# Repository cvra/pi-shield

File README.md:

# CVRA CAN Raspberry Pi Shield

## Features

* Power supply from 12V to 36V to 5V, 3A.
    Powers the Raspberry Pi, and optionally the CAN bus.
* MCP2515 CAN interface (compatible with Linux/SocketCAN) with transceiver and two connectors for daisy chaining.
* Connector for robot's front panel LEDs (dimmable) and pushbuttons.
* Touchscreen connector (I2C for touch, SPI for pixel data)
* DIP switch to discriminate between robots.
* Battery-backed Realtime Clock allows the robot to keep the time even when powered off.
* UART console
* Power control pins, used to cleanly shutdown the Raspberry Pi before shutting power down.
* Socket for a 20 mm DC fan.
* Slot to allow the use of the PiCam camera module.

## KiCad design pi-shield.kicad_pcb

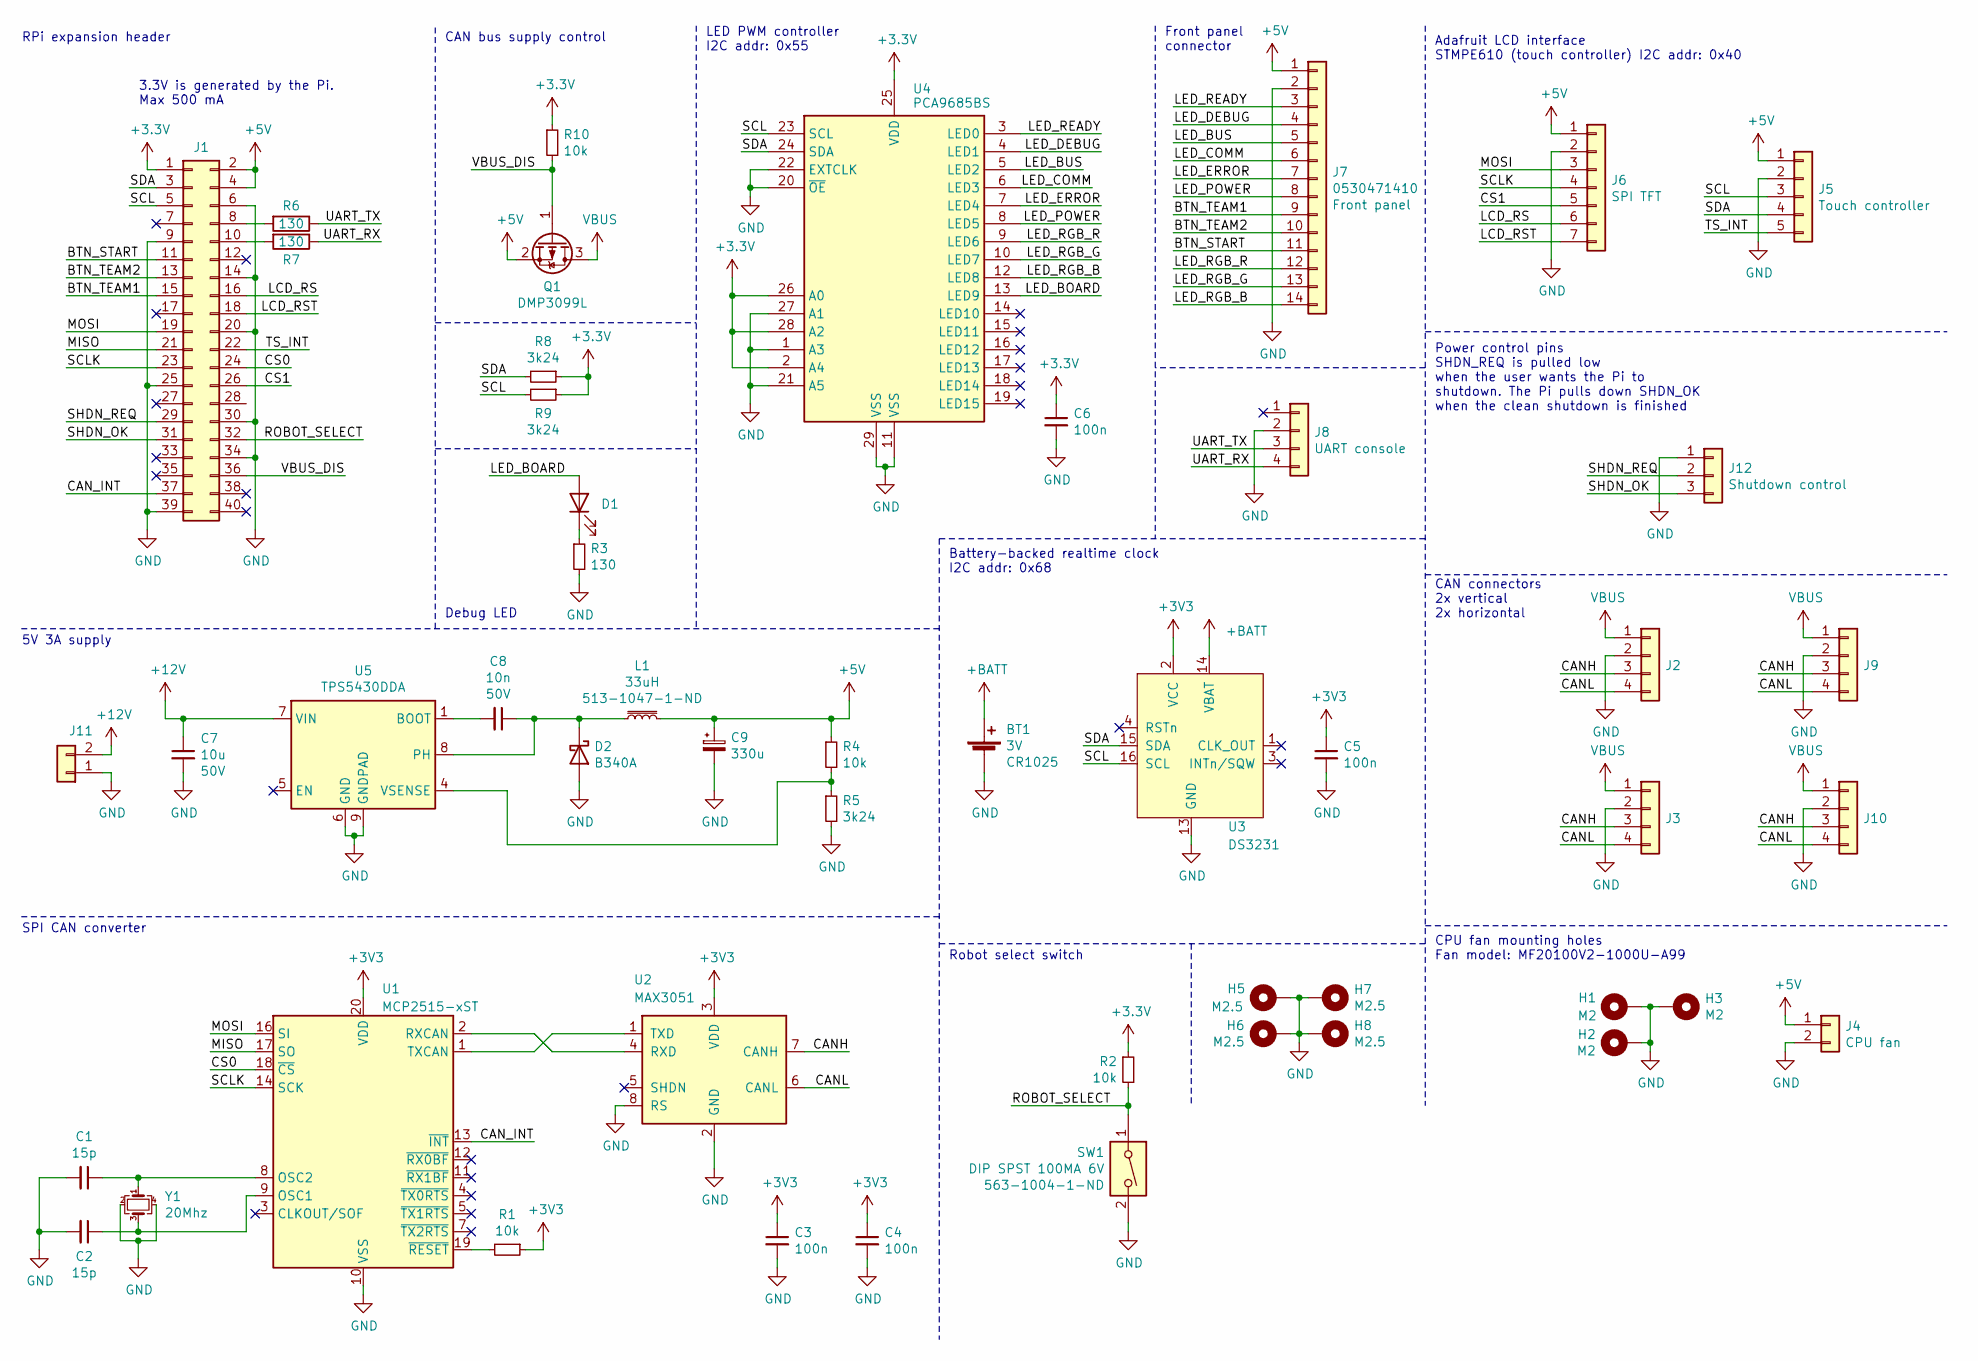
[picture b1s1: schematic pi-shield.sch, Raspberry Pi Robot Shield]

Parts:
BT1: 3V; 3030; digikey# 36-3030-ND
C1: 15p; C_0805_2012Metric_Pad1.15x1.40mm_HandSolder; digikey# 399-17621-1-ND
C2: 15p; C_0805_2012Metric_Pad1.15x1.40mm_HandSolder
C3: 100n; C_0805_2012Metric_Pad1.15x1.40mm_HandSolder; digikey# 399-1169-1-ND
C4, C5, C6: 100n; C_0805_2012Metric_Pad1.15x1.40mm_HandSolder
C7: 10u; C_2220_5650Metric_Pad1.97x5.40mm_HandSolder; voltage 50V; digikey# 445-3492-1-ND
C8: 10n; C_0603_1608Metric_Pad1.05x0.95mm_HandSolder; voltage 50V; digikey# 399-7842-1-ND
C9: 330u; CP_EIA-7343-30_AVX-N_Pad2.25x2.55mm_HandSolder; voltage 6.3V; digikey# 478-4114-1-ND
D1: SML-LXT0805IW-TR; LED_0805_2012Metric_Pad1.15x1.40mm_HandSolder; digikey# 67-1552-1-ND
D2: B340A; D_SMA; digikey# B340A-E3/61TGICT-ND
H1, H2, H3: M2; MountingHole_2.5mm_Pad_Via
H5, H6, H7, H8: M2.5; MountingHole_2.7mm_M2.5_Pad_Via
J1: Conn_02x20_Odd_Even; PinSocket_2x20_P2.54mm_Vertical; digikey# 1568-1462-ND
J2: Conn_01x04; Molex_PicoBlade_53398-0471_1x04-1MP_P1.25mm_Vertical; digikey# WM7608CT-ND
J3: Conn_01x04; Molex_PicoBlade_53398-0471_1x04-1MP_P1.25mm_Vertical
J4: 0530470210; Molex_PicoBlade_53047-0210_1x02_P1.25mm_Vertical; digikey# WM1731-ND
J5: Conn_01x05; Molex_PicoBlade_53048-0510_1x05_P1.25mm_Horizontal; digikey# WM1745-ND
J6: Conn_01x07; Molex_PicoBlade_53048-0710_1x07_P1.25mm_Horizontal; digikey# WM1747-ND
J7: 0530471410; Molex_PicoBlade_53048-1410_1x14_P1.25mm_Horizontal; digikey# WM17004-ND
J8: Conn_01x04; Molex_PicoBlade_53261-0471_1x04-1MP_P1.25mm_Horizontal; digikey# WM7622CT-ND
J9, J10: Conn_01x04; Molex_PicoBlade_53261-0471_1x04-1MP_P1.25mm_Horizontal
J11: 0530470210; Molex_PicoBlade_53398-0271_1x02-1MP_P1.25mm_Vertical; digikey# WM7606CT-ND
J12: Conn_01x03; Molex_PicoBlade_53398-0371_1x03-1MP_P1.25mm_Vertical; digikey# WM7607CT-ND
L1: 33uH; DR127; digikey# 513-1047-1-ND
Q1: DMP3099L; SOT-23; digikey# DMP3099L-13DICT-ND
R1, R2, R4: 10k; R_0603_1608Metric
R3: 130; R_0603_1608Metric; digikey# 311-130GRCT-ND
R5: 3k24; R_0603_1608Metric; digikey# 311-3.24KHRCT-ND
R6, R7: 130; R_0603_1608Metric
R8, R9: 3k24; R_0603_1608Metric
R10: 10k; R_0603_1608Metric; digikey# 311-10.0KHRCT-ND
SW1: DIP SPST 100MA 6V; SW_DIP_SPSTx01_Slide_Copal_CHS-01B_W7.62mm_P1.27mm; digikey# 563-1004-1-ND
U1: MCP2515-xST; TSSOP-20_4.4x6.5mm_P0.65mm; digikey# MCP2515T-I/STCT-ND
U2: MAX3051; SOT-23-8_Handsoldering; digikey# MAX3051EKA+TCT-ND
U3: DS3231; SOIC-16W_7.5x12.8mm_P1.27mm; digikey# DS3231M+TRLCT-ND
U4: PCA9685BS; QFN-28-1EP_6x6mm_P0.65mm_EP4.25x4.25mm; digikey# 568-5305-1-ND
U5: TPS5430DDA; TI_SO-PowerPAD-8_ThermalVias; digikey# 296-35990-1-ND
Y1: 20Mhz; Crystal_SMD_Abracon_ABM3C-4Pin_5.0x3.2mm; digikey# 535-11292-1-ND

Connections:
+5V: C9.1, J1.2, J1.4, J4.1, J5.1, J6.1, J7.1, L1.2, Q1.2 (S), R4.1
+12V: C7.1, J11.2, U5.7 (VIN)
+BATT: BT1.1 (+), U3.14 (VBAT)
/BTN_START: J1.11, J7.11
/BTN_TEAM1: J1.15, J7.9
/BTN_TEAM2: J1.13, J7.10
/CANH: J2.3, J3.3, J9.3, J10.3, U2.7 (CANH)
/CANL: J2.4, J3.4, J9.4, J10.4, U2.6 (CANL)
/CAN_INT: J1.37, U1.13 (~INT)
/CS0: J1.24, U1.18 (~CS)
/CS1: J1.26, J6.5
/LCD_RS: J1.16, J6.6
/LCD_RST: J1.18, J6.7
/LED_BOARD: D1.2 (A), U4.13 (LED9)
/LED_BUS: J7.5, U4.5 (LED2)
/LED_COMM: J7.6, U4.6 (LED3)
/LED_DEBUG: J7.4, U4.4 (LED1)
/LED_ERROR: J7.7, U4.7 (LED4)
/LED_POWER: J7.8, U4.8 (LED5)
/LED_READY: J7.3, U4.3 (LED0)
/LED_RGB_B: J7.14, U4.12 (LED8)
/LED_RGB_G: J7.13, U4.10 (LED7)
/LED_RGB_R: J7.12, U4.9 (LED6)
/MISO: J1.21, U1.17 (SO)
/MOSI: J1.19, J6.3, U1.16 (SI)
/ROBOT_SELECT: J1.32, R2.2, SW1.1
/SCL: J1.5, J5.3, R9.2, U3.16 (SCL), U4.23 (SCL)
/SCLK: J1.23, J6.4, U1.14 (SCK)
/SDA: J1.3, J5.4, R8.2, U3.15 (SDA), U4.24 (SDA)
/SHDN_OK: J1.31, J12.3
/SHDN_REQ: J1.29, J12.2
/TS_INT: J1.22, J5.5
/UART_RX: J8.4, R7.1
/UART_TX: J8.3, R6.1
/VBUS_DIS: J1.36, Q1.1 (G), R10.2
GND: BT1.2 (-), C1.2, C2.2, C3.2, C4.2, C5.2, C6.2, C7.2, C9.2, D2.2 (A), H1.1, H2.1, H3.1, H5.1, H6.1, H7.1, H8.1, J1.6, J1.9, J1.14, J1.20, J1.25, J1.30, J1.34, J1.39, J2.2, J3.2, J4.2, J5.2, J6.2, J7.2, J8.2, J9.2, J10.2, J11.1, J12.1, R3.2, R5.2, SW1.2, U1.10 (VSS), U2.2 (GND), U2.8 (RS), U3.13 (GND), U4.1 (A3), U4.11 (VSS), U4.20 (~OE), U4.21 (A5), U4.22 (EXTCLK), U4.27 (A1), U4.29 (VSS), U5.6 (GND), U5.9 (GNDPAD), Y1.2, Y1.4
unnamed: C1.1, U1.8 (OSC2), Y1.1
unnamed: C2.1, U1.9 (OSC1), Y1.3
unnamed: C8.1, D2.1 (K), L1.1, U5.8 (PH)
unnamed: C8.2, U5.1 (BOOT)
unnamed: D1.1 (K), R3.1
unnamed: J1.8, R6.2
unnamed: J1.10, R7.2
unnamed: R1.2, U1.19 (~RESET)
unnamed: R4.2, R5.1, U5.4 (VSENSE)
unnamed: U1.1 (TXCAN), U2.1 (TXD)
unnamed: U1.2 (RXCAN), U2.4 (RXD)
VBUS: J2.1, J3.1, J9.1, J10.1, Q1.3 (D)

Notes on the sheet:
CPU fan mounting holes Fan model: MF20100V2-1000U-A99
3.3V is generated by the Pi. Max 500 mA
Power control pins SHDN_REQ is pulled low when the user wants the Pi to shutdown. The Pi pulls down SHDN_OK when the clean shutdown is finished
SPI CAN converter
5V 3A supply
RPi expansion header
CAN bus supply control
Debug LED
LED PWM controller I2C addr: 0x55
Robot select switch
Battery-backed realtime clock I2C addr: 0x68
CAN connectors 2x vertical 2x horizontal
Adafruit LCD interface STMPE610 (touch controller) I2C addr: 0x40
Front panel connector

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
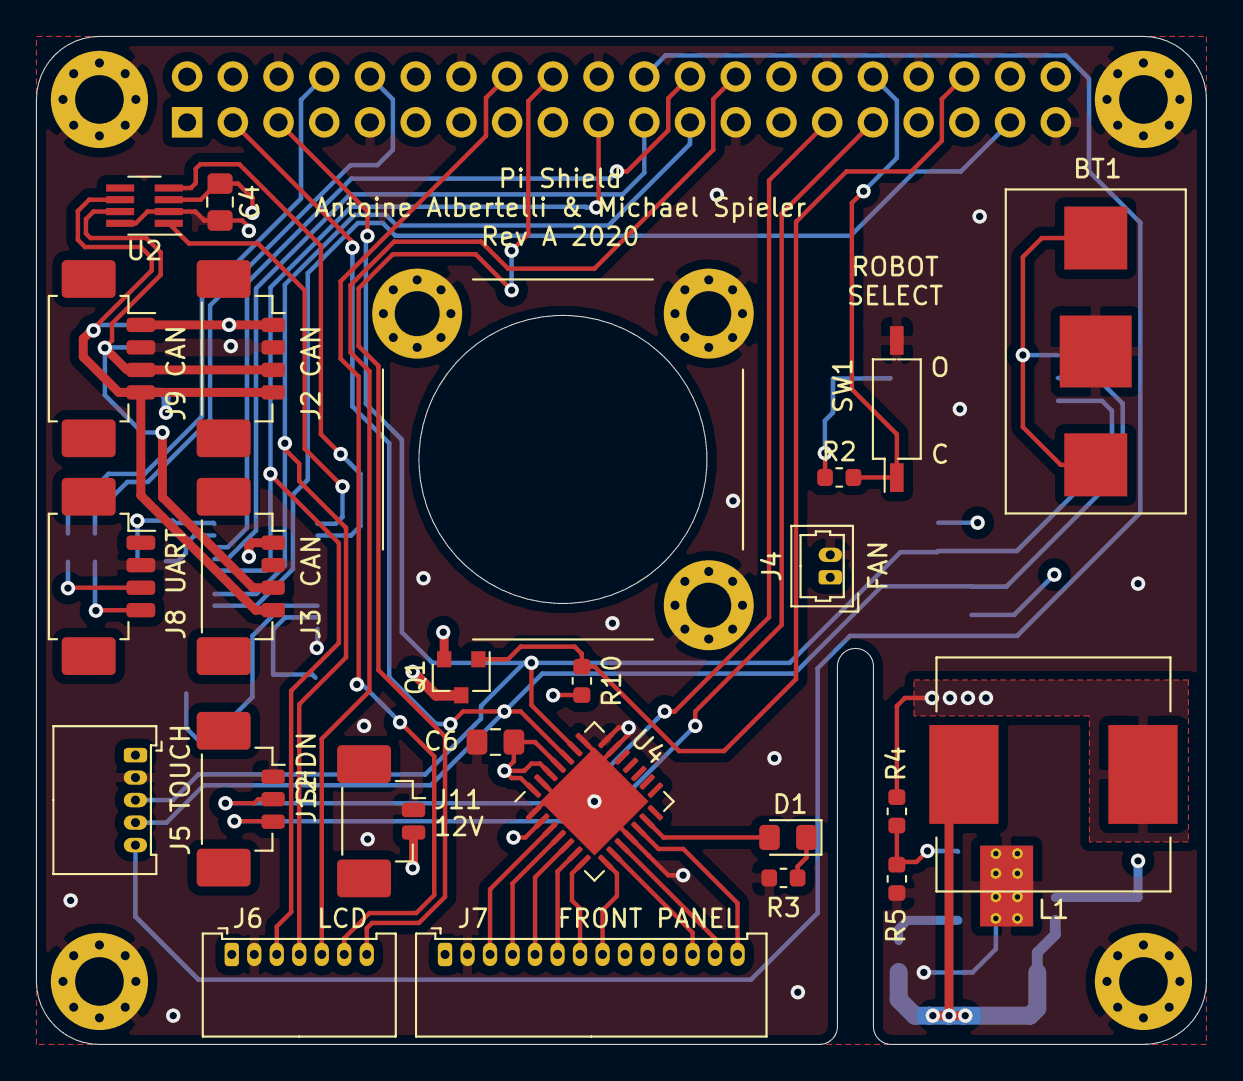
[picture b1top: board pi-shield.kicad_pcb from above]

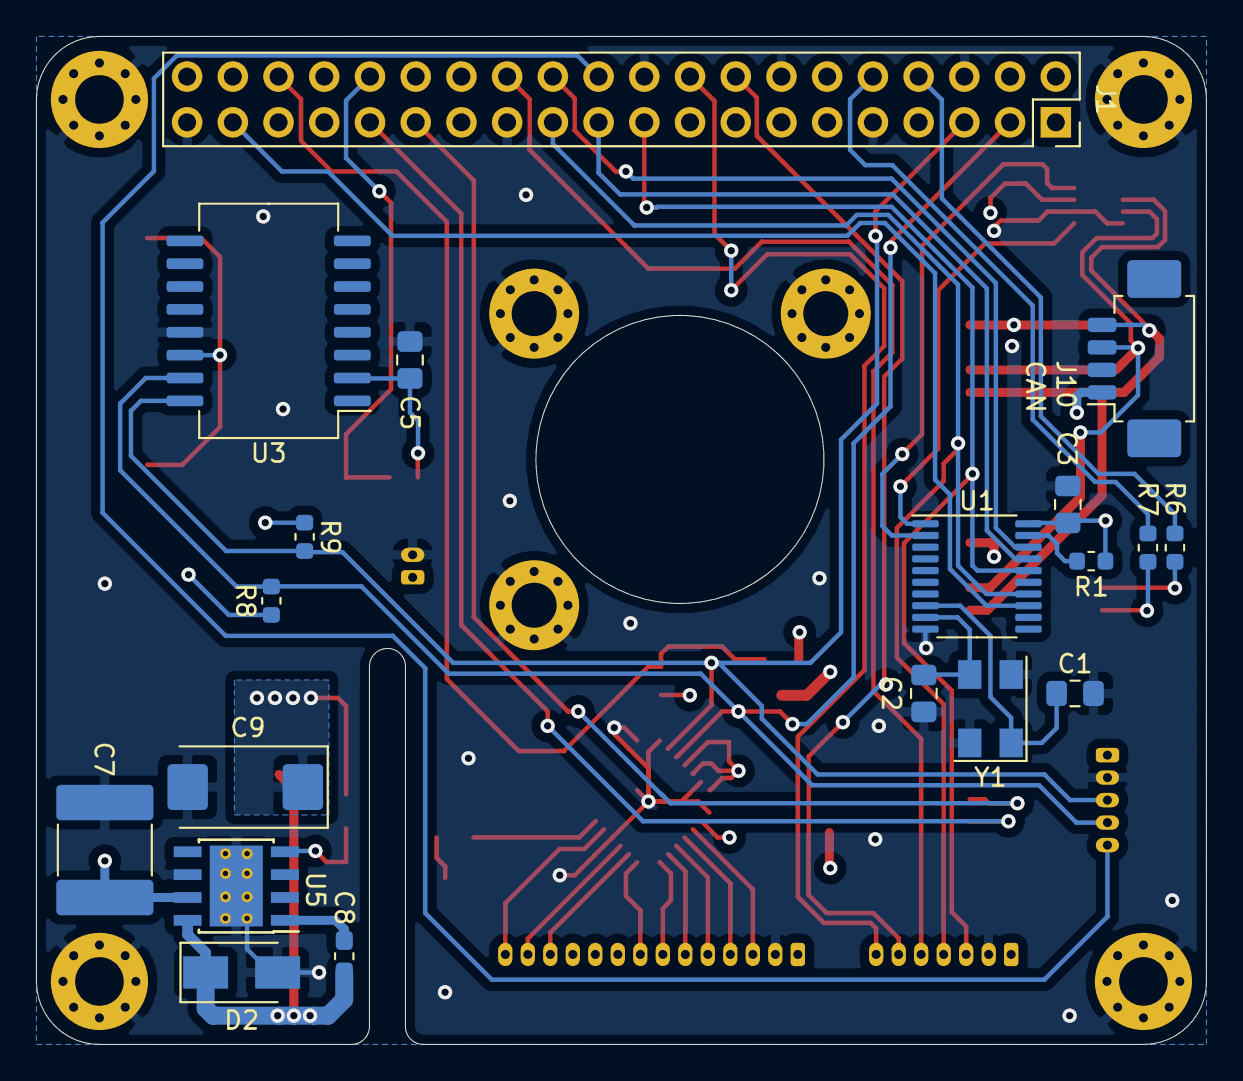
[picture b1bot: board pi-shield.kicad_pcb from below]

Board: 4 copper layers, 65.0 x 56.0 mm, 50 parts (19 on the bottom side), 49 nets.

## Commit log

2020-06-11 First work session with @nuft
2020-06-28 Progressing on pi shield
2020-07-01 Work on some other parts
2020-07-22 Progress on schematic and board outline
2020-08-26 Initial component placement
2020-08-26 Made some progress with layout
2020-09-05 First complete layout
2020-09-05 Add missing 3d object
2020-09-08 Corrections taking into account @nuft remarks
2020-09-08 Prepare for manufacturing adding all digikey#
2020-09-08 Integrate git commit in rev field
2020-09-08 Put full commit hash in comments
2020-09-14 Add fabrication files
2020-09-28 Add a script to generate a BOM in digikey format
2021-09-07 Shape up a bit the README

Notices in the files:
pi-shield.sch:
CC-BY-SA
